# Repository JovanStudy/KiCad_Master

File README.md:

# MOOG_PRODIGY_PROJECT

## 📁 Prototip organizacije

```text
MOOG_PRODIGY_PROJECT/
│
├── schematics/
│   ├── schematics_lvl1/
│   │   └── system_overview.kicad_sch
│   │
│   ├── schematics_lvl2/
│   │   ├── power_supply.kicad_sch
│   │   ├── mcu_core.kicad_sch
│   │   ├── communication.kicad_sch
│   │   └── peripherals.kicad_sch
│   │
│   └── schematics_lvl3/
│       ├── usb_interface.kicad_sch
│       ├── sensors.kicad_sch
│       └── motor_driver.kicad_sch
│
├── pcb/
│   ├── pcb_main.kicad_pcb
│   ├── pcb_panelization.kicad_pcb
│   └── stackup.md
│
├── libraries/
│   ├── symbols/
│   ├── footprints/
│   └── 3d_models/
│
├── bom/   (Bill of Materials – spisak uključenih komponenti)
│   ├── bom.csv
│   └── bom.xlsx
│
├── manufacturing/
│   ├── gerbers/
│   ├── drill/
│   ├── pick_and_place/
│   └── assembly_notes.md
│
├── simulations/
│   ├── spice/
│   └── signal_integrity/
│
└── README.md
```

---

## 📐 PCB Design Rules (EU Baseline)

```text
PCB Design Rules
│
├── Track Width
│   ├── Signal (Single-Width)
│   │   └── 0.20 mm (default, EU safe)
│   │
│   └── Power (Power-Width)
│       ├── 0.50 mm (≤ 1 A)
│       ├── 1.00 mm (2–3 A, 1 oz Cu)
│       └── Polygon Pour (high current)
│
├── Clearance
│   ├── Signal ↔ Signal
│   │   └── 0.20 mm
│   ├── Signal ↔ Power
│   │   └── 0.20 mm
│   ├── Power ↔ Power
│   │   └── 0.20 mm
│   └── High Voltage
│       ├── 230 VAC → ≥ 3.0 mm
│       └── 400 VDC → 4–6 mm (creepage)
│
├── Vias
│   ├── Via Drill
│   │   └── 0.30 mm
│   ├── Via Diameter
│   │   └── 0.60 mm
│   └── Annular Ring
│       └── 0.15 mm
│
├── Pads (THT)
│   ├── Rule
│   │   └── Pad = Drill + 0.6 mm
│   └── Example
│       └── 0.8 mm drill → 1.4 mm pad
│
├── Copper
│   ├── Standard
│   │   └── 1 oz (35 µm)
│   └── Power Boards
│       └── 2 oz (70 µm)
│
└── Solder Mask & Silk
    ├── Mask Expansion
    │   └── 0.05 – 0.10 mm
    ├── Min Silk Width
    │   └── 0.15 mm
    └── Min Text Height
        └── 1.0 mm
```

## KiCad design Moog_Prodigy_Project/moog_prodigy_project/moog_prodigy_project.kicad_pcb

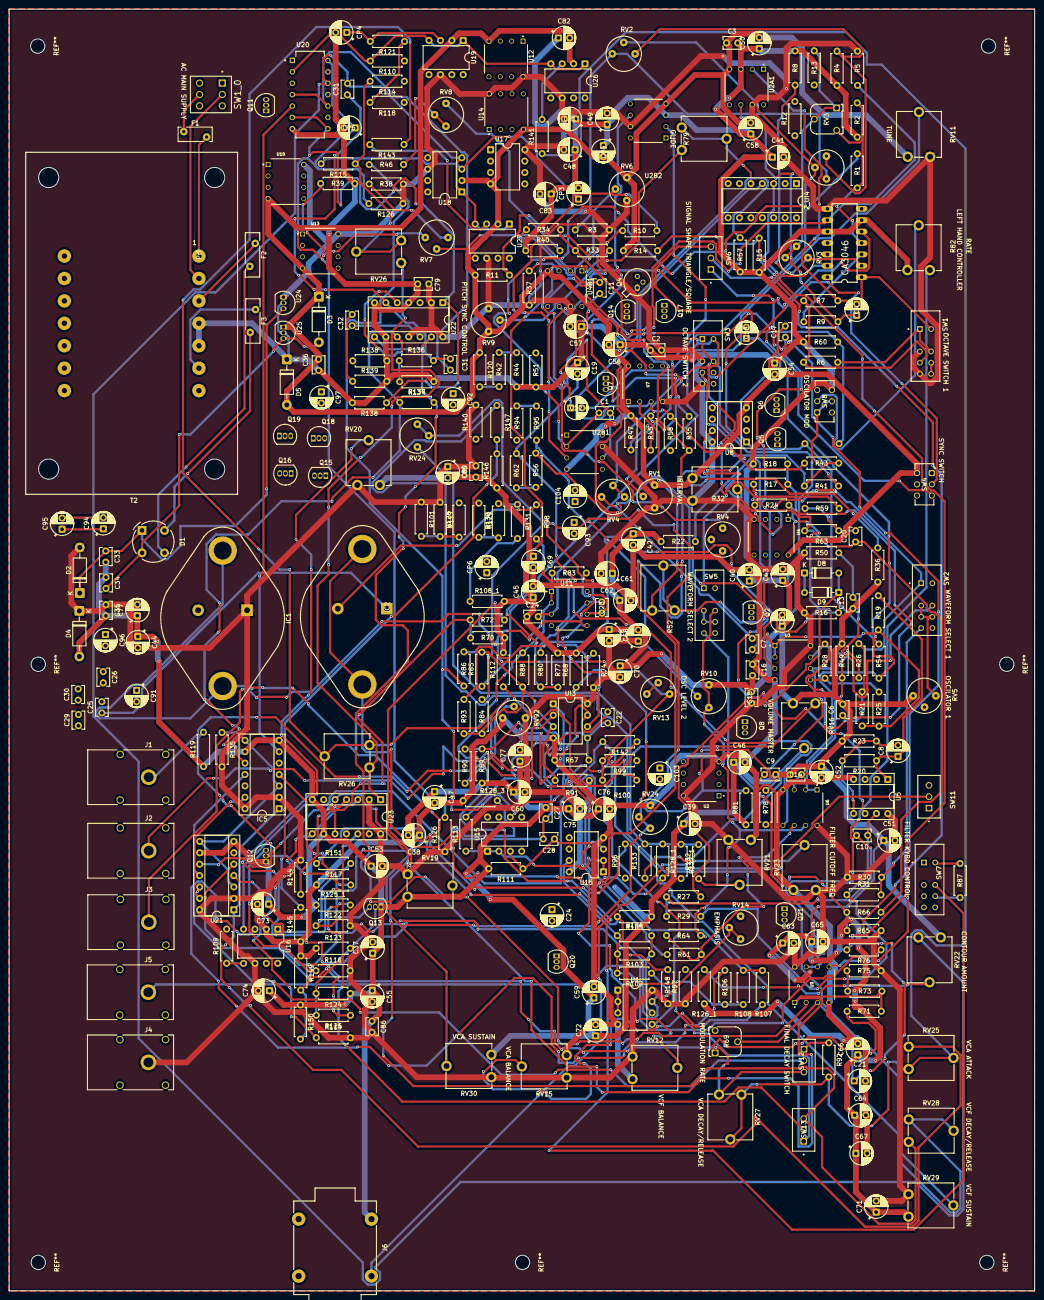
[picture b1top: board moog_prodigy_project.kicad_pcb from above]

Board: 2 copper layers, 228.6 x 285.8 mm, 378 parts (1 on the bottom side), 186 nets.

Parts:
2_UI4: MC14007UBCP; DIP-14_W7.62mm_Socket
C1, C10, C20: 10p; C_Disc_D3.8mm_W2.6mm_P2.50mm
C2, C3, C6, C11, C13, C14, C15, C16, C22, C23, C31, C31#2, C32: 10n; C_Disc_D3.8mm_W2.6mm_P2.50mm
C4, C8, C12, C18: 47p; CP_Radial_D5.0mm_P2.50mm
C5: 1000n; CP_Radial_D5.0mm_P2.50mm
C7, C17: 1n; C_Disc_D3.8mm_W2.6mm_P2.50mm
C9: 500p; C_Disc_D3.8mm_W2.6mm_P2.50mm
C19: 500p; CP_Radial_D5.0mm_P2.50mm
C21: 2u7/25V; CP_Radial_D5.0mm_P2.50mm
C24: 1u/25V; CP_Radial_D5.0mm_P2.50mm
C24#2: 1000n; C_Disc_D3.8mm_W2.6mm_P2.50mm
C25, C26, C27, C29, C30: 27n; C_Disc_D3.8mm_W2.6mm_P2.50mm
C28, C33, C34, C35, C36, C79, C80, C86: 100n; C_Disc_D3.8mm_W2.6mm_P2.50mm
C37, C38, C39, C40, C41, C42, C43, C44, C45, C46, C47, C48, C49, C50, C51, C52, C53, C54, C55, C56, C57, C58, C59, C60, C61, C62, C63, C64, C65, C66, C67, C68, C69, C70, C71, C72, C73, C74, C75, C76, C77, C77#2, C78, C81, C82, C83, C84, C85: 100n; CP_Radial_D5.0mm_P2.50mm
C91, C92: 6u8/25V; CP_Radial_D5.0mm_P2.50mm
C93: 10u/16V; CP_Radial_D5.0mm_P2.50mm
C94, C95: 1000u/35V; CP_Radial_D5.0mm_P2.50mm
C96, C97: 10u/25V; CP_Radial_D5.0mm_P2.50mm
C103: 220u/6V3; CP_Radial_D5.0mm_P2.50mm
C104: 2u2/16V; CP_Radial_D5.0mm_P2.50mm
CA3046: CA3046; DIL14
CP3, CP4: 6.8u; CP_Radial_D5.0mm_P2.50mm
CP5: 10u; CP_Radial_D5.0mm_P2.50mm
CP6: 220u; CP_Radial_D5.0mm_P2.50mm
D1: B40R; Diode_Bridge_Round_D9.0mm
D2, D3, D4, D5: 1N4001; D_DO-41_SOD81_P10.16mm_Horizontal
D8, D9: 1N4148; D_DO-35_SOD27_P7.62mm_Horizontal
F1: 125mA/T; Fuse_Bourns_MF-RHT050
F2, F3: 1A/F; Fuse_Bourns_MF-RHT100
IC1, IC2: 2N3055; TO-3
IC5: MC14007UBCP; DIP-14_W7.62mm_Socket
J1: P2-3; Banana_Cliff_FCR7350B_S16N-PC_Horizontal
J2: P2-4; Banana_Cliff_FCR7350B_S16N-PC_Horizontal
J3: P2-2; Banana_Cliff_FCR7350B_S16N-PC_Horizontal
J4, J5: P2-1; Banana_Cliff_FCR7350B_S16N-PC_Horizontal
J6: NJ2FD-V; Jack_6.35mm_Neutrik_NMJ4HCD2_Horizontal
Q2, Q5, Q6: E112; TO-92_Inline
Q4: BC549; TO-18-3
Q7, Q8, Q11, Q20, Q21: BC549; TO-92_Inline
Q12, Q13: BC327; TO-92_Inline
Q14, Q15, Q16, Q17, Q18, Q19: BC550C; TO-92_Inline
R1: 121K; R_Axial_DIN0207_L6.3mm_D2.5mm_P7.62mm_Horizontal
R2, R8, R36, R40, R83, R106, R108, R111, R112, R115, R121, R126, R126#2, R141, R143: 100; R_Axial_DIN0207_L6.3mm_D2.5mm_P7.62mm_Horizontal
R3: 63K4; R_Axial_DIN0207_L6.3mm_D2.5mm_P7.62mm_Horizontal
R4, R39: 3K01; R_Axial_DIN0207_L6.3mm_D2.5mm_P7.62mm_Horizontal
R5, R9, R27, R37, R38, R59, R73, R75, R86, R88, R97, R116, R122, R132, R133, R139, R144, R148: 100K; R_Axial_DIN0207_L6.3mm_D2.5mm_P7.62mm_Horizontal
R6, R7: 2M; R_Axial_DIN0207_L6.3mm_D2.5mm_P7.62mm_Horizontal
R10, R71: 22K 10%; R_Axial_DIN0207_L6.3mm_D2.5mm_P7.62mm_Horizontal
R11, R47: 15K; R_Axial_DIN0207_L6.3mm_D2.5mm_P7.62mm_Horizontal
R12: 470; R_Axial_DIN0207_L6.3mm_D2.5mm_P7.62mm_Horizontal
R13, R77: 4K75 1%; R_Axial_DIN0207_L6.3mm_D2.5mm_P7.62mm_Horizontal
R14, R16, R50, R110: 20K 5%; R_Axial_DIN0207_L6.3mm_D2.5mm_P7.62mm_Horizontal
R15, R44, R92, R96, R98, R99, R102, R103, R109, R113, R114#2, R118, R142: 1K; R_Axial_DIN0207_L6.3mm_D2.5mm_P7.62mm_Horizontal
R17, R19, R54: 2K; R_Axial_DIN0207_L6.3mm_D2.5mm_P7.62mm_Horizontal
R18: 18K2; R_Axial_DIN0207_L6.3mm_D2.5mm_P7.62mm_Horizontal
R20, R41, R43, R55, R100, R136: 1M; R_Axial_DIN0207_L6.3mm_D2.5mm_P7.62mm_Horizontal
R21, R22, R23, R24, R25, R26, R28, R30, R31, R49, R56, R57, R58, R60, R61, R62, R64, R65, R66, R70, R81, R114, R119, R124, R135, R137, R138, R138#2, R140, R146, R150: 10K; R_Axial_DIN0207_L6.3mm_D2.5mm_P7.62mm_Horizontal
R29: 5M1 1%; R_Axial_DIN0207_L6.3mm_D2.5mm_P7.62mm_Horizontal
R32: 10K LIN; Potentiometer_ACP_CA9-V10_Vertical
R33: 82K5; R_Axial_DIN0207_L6.3mm_D2.5mm_P7.62mm_Horizontal
R34: 120K; R_Axial_DIN0207_L6.3mm_D2.5mm_P7.62mm_Horizontal
R35: 10; R_Axial_DIN0207_L6.3mm_D2.5mm_P7.62mm_Horizontal
R42: 11K8; R_Axial_DIN0207_L6.3mm_D2.5mm_P7.62mm_Horizontal
R45: 22K; R_Axial_DIN0207_L6.3mm_D2.5mm_P7.62mm_Horizontal
R46: 4K75; R_Axial_DIN0207_L6.3mm_D2.5mm_P7.62mm_Horizontal
R51: 1K6 5%; R_Axial_DIN0207_L6.3mm_D2.5mm_P7.62mm_Horizontal
R52, R82: 10K; Potentiometer_ACP_CA9-V10_Vertical
R63, R74, R85: 5M1; R_Axial_DIN0207_L6.3mm_D2.5mm_P7.62mm_Horizontal
R67: 14K3; R_Axial_DIN0207_L6.3mm_D2.5mm_P7.62mm_Horizontal
R68: 18K 5%; R_Axial_DIN0207_L6.3mm_D2.5mm_P7.62mm_Horizontal
R69: 2M5; Potentiometer_Runtron_RM-065_Vertical
R72: 62K 5%; R_Axial_DIN0207_L6.3mm_D2.5mm_P7.62mm_Horizontal
R76: 5M; R_Axial_DIN0207_L6.3mm_D2.5mm_P7.62mm_Horizontal
R78: 30K 5%; R_Axial_DIN0207_L6.3mm_D2.5mm_P7.62mm_Horizontal
R79: 5M1; Potentiometer_ACP_CA9-V10_Vertical
R80: 2K2; R_Axial_DIN0207_L6.3mm_D2.5mm_P7.62mm_Horizontal
R84: 750K; R_Axial_DIN0207_L6.3mm_D2.5mm_P7.62mm_Horizontal
R87, R127_1: 60K4; R_Axial_DIN0207_L6.3mm_D2.5mm_P7.62mm_Horizontal
R89: 43K2; R_Axial_DIN0207_L6.3mm_D2.5mm_P7.62mm_Horizontal
R90: 2M43; R_Axial_DIN0207_L6.3mm_D2.5mm_P7.62mm_Horizontal
R91: 332K; R_Axial_DIN0207_L6.3mm_D2.5mm_P7.62mm_Horizontal
R93: 205K; R_Axial_DIN0207_L6.3mm_D2.5mm_P7.62mm_Horizontal
R94, R95: 120K 5%; R_Axial_DIN0207_L6.3mm_D2.5mm_P7.62mm_Horizontal
R101, R127, R128, R129, R130, R131: 150; R_Axial_DIN0207_L6.3mm_D2.5mm_P7.62mm_Horizontal
R104, R105: 6K81; R_Axial_DIN0207_L6.3mm_D2.5mm_P7.62mm_Horizontal
R107: 51K; R_Axial_DIN0207_L6.3mm_D2.5mm_P7.62mm_Horizontal
R108_1, R120: 200; R_Axial_DIN0207_L6.3mm_D2.5mm_P7.62mm_Horizontal
R117, R123, R145: 56K; R_Axial_DIN0207_L6.3mm_D2.5mm_P7.62mm_Horizontal
R125: 4K3; R_Axial_DIN0207_L6.3mm_D2.5mm_P7.62mm_Horizontal
R125_1: 953; R_Axial_DIN0207_L6.3mm_D2.5mm_P7.62mm_Horizontal
R126_1: 51K 5%; R_Axial_DIN0207_L6.3mm_D2.5mm_P7.62mm_Horizontal
R128_1: 36K; R_Axial_DIN0207_L6.3mm_D2.5mm_P7.62mm_Horizontal
R128_3: 36K 5%; R_Axial_DIN0207_L6.3mm_D2.5mm_P7.62mm_Horizontal
R134: 100k; R_Axial_DIN0207_L6.3mm_D2.5mm_P7.62mm_Horizontal
R147, R151: 4K32; R_Axial_DIN0207_L6.3mm_D2.5mm_P7.62mm_Horizontal
R149: 56K2; R_Axial_DIN0207_L6.3mm_D2.5mm_P7.62mm_Horizontal
RV1, RV4, RV4#2, RV6, RV92: 10K; Potentiometer_Bourns_3339P_Vertical_HandSoldering
RV2, RV2#2, RV3, RV7, RV8: 500; Potentiometer_Bourns_3339P_Vertical_HandSoldering
RV3#2: 500; Potentiometer_Runtron_RM-065_Vertical
RV5, RV9, RV10: 10K LIN; Potentiometer_Bourns_3339P_Vertical_HandSoldering
RV11: 10K LOG; Potentiometer_ACP_CA9-V10_Vertical
RV12, RV15: 100K LIN; Potentiometer_ACP_CA9-V10_Vertical
RV13: 1K; Potentiometer_Bourns_3339P_Vertical_HandSoldering
RV14: 51K1 LOG; Potentiometer_Bourns_3339P_Vertical_HandSoldering
RV16: 5K LOG; Potentiometer_ACP_CA9-V10_Vertical
RV19, RV20: 10K; Potentiometer_ACP_CA9-V10_Vertical
RV21: 100K; Potentiometer_ACP_CA9-V10_Vertical
RV22, RV23: 50K; Potentiometer_ACP_CA9-V10_Vertical
RV24, RV24#2: 250; Potentiometer_Bourns_3339P_Vertical_HandSoldering
RV25, RV26, RV27: 1M LOG; Potentiometer_ACP_CA9-V10_Vertical
RV26#2, RV28: 1M; Potentiometer_ACP_CA9-V10_Vertical
RV29, RV30: 10K LIN; Potentiometer_ACP_CA9-V10_Vertical
SW1, SW2, SW3, SW5, SW7: Switch_4x4; SW_SLW-1575662-5A-S-D
SW1_0: 200MDP1T1B1M2QEH; SW_200MDP1T1B1M2QEH
SW4, SW8: SW_Slide_DPDT_3x3; SW_CK_JS202011CQN_DPDT_Straight
SW6: Switch_1x3; SW_ATE1D-2M3-10-Z
SW11: FILTER MODE; SW_ATE1D-2M3-10-Z
SW12, SW13: FINAL DECAY SWITCH; SW_ATE1D-2M3-10-Z
T2: 230VAC / 2x15VAC 0A53 16VA; Transformer_CHK_EI54-16VA_2xSec
U1, U17: NE5532; DIP-8_W7.62mm
U2, U3, U4, U6, U7, U9, U13: NE5532; DIP794W45P254L1016H508Q8
U2A1, U2B1, U2B2, U4B1, U12, U14: OPA134; DIP794W45P254L959H508Q8
U5, U8: LT1011CN8; DIP-8_W7.62mm_Socket
U10: DIP794W45P254L1016H508Q8
U11: OPA234; DIP794W45P254L959H508Q8
U15, U15#2: LT1469; DIP-8_W7.62mm
U16: LT1228; DIP-8_W7.62mm
U18, U19, U26, U27: OPA184; DIP-8_W7.62mm
U20: NE556N; DIP794W45P254L1930H508Q14
U21, U22, U23: MC14007UBCP; DIP-14_W7.62mm_Socket
U24: LM7812; TO-92_Inline
U25: LM7912; TO-92_Inline
UI3: NE5532; DIP-8_W7.62mm

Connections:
+12V: C2.2, C15.2, C35.1, C37.2, C39.2, C41.2, C43.2, C44.2, C48.2, C49.2, C51.2, C53.2, C55.2, C57.2, C60.2, C62.2, C63.2, C65.2, C68.2, C70.2, C71.2, C74.2, C75.2, C77.2, C77#2.2, C78.1, C79.2, C80.2, C81.2, C83.2, C85.1, C86.2, CA3046.8, D2.2 (A), D4.1 (K), IC1.1 (C), IC5.2, IC5.14, J4.1, R3.1, R5.1, R16.1, R30.2, R32.1, R37.1, R38.1, R50.2, R65.2, R74.2, R75.1, R91.1, R97.1, R101.1, R114.2, R116.2, R122.2, R126.1, R126#2.1, R127.1, R135.2, R140.2, R144.2, R148.2, RV1.1, RV6.1, RV9.1, RV11.1, RV12.3, RV15.3, RV19.3, RV20.3, RV21.1, RV23.1, RV29.3, RV30.3, RV92.3, SW1.2, SW1.4, SW3.2, SW3.4, U1.8, U2.8, U2A1.7, U2B1.7, U2B2.7, U3.8, U4.4, U4B1.7, U5.8, U6.8, U7.4, U8.8, U9.8, U10.8, U12.8, U13.8, U14.8, U15#2.8 (V+), U16.6, U17.8, U18.6 (V+), U19.6 (V+), U21.2, U21.14, U22.2, U22.11, U22.14, U23.2, U23.14, U24.1 (VO), U26.6, U27.6, UI3.8
-12V: C3.1, C16.1, C21.2, C36.2, C38.1, C40.2, C42.2, C45.2, C46.2, C47.2, C50.2, C52.2, C54.2, C56.2, C58.2, C59.2, C61.2, C64.2, C66.2, C67.2, C69.2, C72.2, C73.2, C76.2, C82.2, C84.2, D3.1 (K), D5.2 (A), R11.1, R14.1, R32.3, R47.1, R67.2, R117.1, R120.1, R123.1, R126_1.2, R128_3.1, R145.1, R149.1, RV1.3, RV6.3, RV9.3, RV11.3, RV12.1, RV15.1, RV21.3, RV23.3, RV24.3, RV92.1, SW4.6 (C), U1.4, U2.4, U2A1.4, U2B1.4, U2B2.4, U3.4, U4.8, U4B1.4, U5.4, U6.4, U7.8, U8.4, U9.4, U10.4, U12.4, U13.4, U14.4, U15#2.4 (V-), U16.2, U17.4, U18.2 (V-), U19.2 (V-), U25.1 (VO), U26.2, U27.2, UI3.4
Flag to R87: R46.1, R86.2, UI3.1
Flag to R94: R95.2, RV10.2
Flag to U6A: C8.1, R19.2, R20.1, U5.1
GND: C2.1, C3.2, C5.1, C6.2, C9.1, C13.1, C14.1, C15.1, C16.2, C19.1, C24#2.1, C27.1, C33.2, C34.1, C35.2, C36.1, C37.1, C38.2, C39.1, C40.1, C41.1, C42.1, C43.1, C44.1, C45.1, C46.1, C47.1, C48.1, C49.1, C50.1, C51.1, C52.1, C53.1, C54.1, C55.1, C56.1, C57.1, C58.1, C59.1, C60.1, C61.1, C62.1, C63.1, C64.1, C65.1, C66.1, C67.1, C68.1, C69.1, C70.1, C71.1, C72.1, C73.1, C74.1, C75.1, C76.1, C77.1, C77#2.1, C78.2, C79.1, C80.1, C81.1, C82.1, C83.1, C84.1, C85.2, C86.1, CA3046.6, CA3046.10, CP3.2, CP4.2, CP5.2, D4.2 (A), D5.1 (K), IC5.7, IC5.9, J6.T, Q12.1 (C), Q13.1 (C), R2.2, R4.2, R8.1, R15.1, R18.2, R22.2, R23.2, R36.2, R39.2, R40.1, R44.1, R49.1, R51.2, R57.2, R60.2, R68.2, R70.2, R77.2, R81.1, R82.3, R89.1, R105.1, R108_1.2, R111.2, R112.2, R119.1, R124.1, R125_1.1, R134.1, R138.2, R138#2.2, R139.2, R146.1, R150.1, RV5.3, RV10.3, RV16.1, RV19.1, RV20.1, RV22.3, RV29.1, RV30.1, SW8.4 (A), T2.4 (SB), T2.5 (SC), U2A1.3 (+), U2B2.3 (+), U20.7 (GND), U21.7, U21.9, U22.4, U22.7, U22.9, U23.7, U23.9, U24.2 (GND), U25.2 (GND)
Input to C39: R94.2, R95.1
Input to VCA/VCF: 2_UI4.3, R76.2
Input to diode protection: D8.1 (K), D9.2 (A)
unnamed: 2_UI4.5, R79.2, R79.3
unnamed: R73.1, R75.2
unnamed: C1.2, R10.1, U2B1.6
unnamed: C4.1, R9.1, U2A1.6
unnamed: C7.1, RV4#2.1
unnamed: C10.1, R29.2, R31.1, U5.7
unnamed: C11.2, R45.1, U4B1.6
unnamed: C12.1, U2B2.6
unnamed: C17.1, R52.1, R52.2
unnamed: C18.1, R54.1, R55.1, U8.1
unnamed: C20.1, R63.2, R66.1, U8.7
unnamed: C23.1, R80.2, U11.7
unnamed: C27.2, C28.2, R112.1, U16.1
unnamed: C31.1, C31#2.1, R136.2, U22.6
unnamed: C32.1, U22.12
unnamed: C32.2, R139.1, U22.3
unnamed: RV13.1, RV13.2
unnamed: R98.2, R99.2, R100.1, RV13.3
unnamed: IC2.2 (B), R98.1
unnamed: RV4.2, RV4.3
unnamed: CA3046.2, R8.2, RV3.3
unnamed: CA3046.3, R9.2
unnamed: CA3046.4, R1.2, R2.1, RV3#2.3
unnamed: CA3046.7, R12.2
unnamed: CA3046.13, R14.2, R15.2
unnamed: R40.2, RV8.3
unnamed: R33.2, R34.2, R35.1, R36.1
unnamed: R42.2, R44.2
unnamed: C33.1, D1.1 (+), D2.1 (K), U24.3 (VI)
unnamed: C34.2, D1.2 (-), D3.2 (A), U25.3 (VI)
unnamed: D1.3, F2.2
unnamed: D1.4, F3.2
unnamed: D8.2 (A), D9.1 (K), R84.1
unnamed: F1.1, SW1_0.5
unnamed: IC1.3 (E), R102.2, R103.2, R105.2, R106.2, R108.2
unnamed: R101.2, R127.2, R128.1
unnamed: IC2.3 (E), R96.2
unnamed: C22.2, J1.1, R67.1, UI3.5 (+)
unnamed: C22.1, J2.1, UI3.7
unnamed: J3.1, R74.1, U11.5 (+)
unnamed: J5.1, R76.1
unnamed: J6.S, RV16.2
unnamed: R10.2, R11.2
unnamed: R21.1, R22.1, R24.1, R26.1, R27.1, SW2.1
unnamed: R45.2, R47.2
unnamed: R56.1, R62.1
unnamed: R57.1, R58.1, R59.2, SW5.1, U7.3 (-)
unnamed: Q12.2 (B), R117.2, R119.2
unnamed: Q13.2 (B), R123.2, R124.2, R125.2
unnamed: R128.2, R129.1
unnamed: R129.2, R130.1
unnamed: R130.2, R131.1
unnamed: C25.1, IC2.1 (C)
unnamed: R145.2, R146.2, R147.2
unnamed: R144.1, U23.4
unnamed: R149.2, R150.2, R151.2
unnamed: R148.1, U21.4
unnamed: R1.1, RV1.2
unnamed: R3.2, RV2.1, RV2#2.1
unnamed: R4.1, RV2.3, RV2#2.3
unnamed: R6.1, R7.1, SW1.3
unnamed: R6.2, SW1.1, SW1.6
unnamed: R13.2, RV3.1, RV3.2, RV3#2.1, RV3#2.2
unnamed: R28.2, SW2.6, U3.7
unnamed: R30.1, R31.2, SW2.4
unnamed: R32.2, R33.1
unnamed: R34.1, RV6.2
unnamed: R35.2, SW4.3 (C)
unnamed: R38.2, RV7.1
unnamed: R39.1, RV7.3
unnamed: R41.1, R43.1, SW3.3
unnamed: R41.2, SW3.1, SW3.6
unnamed: R46.2, RV8.1, RV8.2
unnamed: R56.2, R61.1
unnamed: R64.2, RV10.1, SW5.6, U6.7
unnamed: R65.1, R66.2, SW5.4
unnamed: R69.1, R71.2
unnamed: R71.1, R72.1, R73.2, U9.1
unnamed: R77.1, R79.1, R80.1
unnamed: R85.1, RV11.2
unnamed: R87.1, SW7.5
unnamed: R87.2, SW7.7
unnamed: R90.2, RV92.2
unnamed: R100.2, RV12.2
unnamed: R104.1, RV14.1, RV14.2, U1.7, U15#2.7
unnamed: R107.1, RV15.2
unnamed: R109.1, U16.5
unnamed: R113.2, RV16.3
unnamed: R114.1, U23.3, U23.8
unnamed: R42.1, R120.2
unnamed: R125.1, RV20.2
unnamed: R125_1.2, RV24.1, RV24.2, RV24#2.1, RV24#2.2
unnamed: R126_1.1, RV22.2
unnamed: R132.1, RV21.2
unnamed: R133.1, RV23.2
unnamed: IC5.3, IC5.8, R135.1, U21.3, U21.8
unnamed: IC5.10, R137.1, U22.5, U22.10
unnamed: R137.2, U21.10, U22.8, U22.13, U23.10
unnamed: R92.2, R141.1, RV25.1, RV25.2, RV27.2, RV27.3
unnamed: R142.2, R143.1, RV26.1, RV26.2, RV28.2, RV28.3
unnamed: R147.1, RV29.2
unnamed: R151.1, RV30.2
unnamed: RV5.1, SW2.2, SW2.3, SW2.7
unnamed: RV9.2, SW4.2 (B)
unnamed: IC5.1, RV25.3, U21.1
unnamed: RV26.3, RV26#2.3, U23.1
unnamed: SW1.7, SW1.8
unnamed: SW5.2, SW5.3, SW5.7
unnamed: C21.1, R69.2, SW6.1 (A), U9.3 (+)
unnamed: SW6.2 (B), U9.5 (+)
unnamed: R78.1, R81.2, SW6.3 (C)
unnamed: R128_1.2, R128_3.2, SW11.2 (B)
unnamed: R92.1, SW12.1 (A)
unnamed: SW12.2 (B), U21.12
unnamed: RV27.1, SW12.3 (C), U21.5
unnamed: R142.1, SW13.1 (A)
unnamed: SW13.2 (B), U23.12
unnamed: RV28.1, SW13.3 (C), U23.5
unnamed: F1.2, T2.1 (AA)
unnamed: SW1_0.2, T2.2 (AB)
unnamed: F2.1, T2.3 (SA)
unnamed: F3.1, T2.6 (SD)
unnamed: R102.1, U1.5 (+)
unnamed: R103.1, R104.2, U1.6 (-)
unnamed: C4.2, CA3046.1, R7.2, SW1.5, U2A1.2 (-)
unnamed: CA3046.9, R5.2, U2B1.3 (+)
unnamed: C1.1, RV2.2, RV2#2.2, U2B1.2 (-)
unnamed: C12.2, R43.2, SW3.5, U2B2.2 (-)
unnamed: C5.2, R16.2, R17.1, U3.3 (+)
unnamed: C7.2, R19.1, R21.2, R25.1, U3.1, U3.2 (-)
unnamed: R25.2, R28.1, U3.5 (+)
unnamed: C9.2, R26.2, U3.6 (-)
unnamed: CA3046.5, RV4#2.2, RV4#2.3
unnamed: R37.2, U4B1.3 (+)
unnamed: C11.1, RV7.2, U4B1.2 (-)
unnamed: C8.2, R20.2, R23.1, U5.5 (+)
unnamed: R24.2, U5.6 (-)
unnamed: C10.2, R27.2, R29.1
unnamed: C6.1, R17.2, R18.1
unnamed: C13.2, C14.2, R49.2, R50.1, U6.3 (+)
unnamed: C17.2, R54.2, U6.1, U6.2 (-)
unnamed: C19.2, R62.2, U6.5 (+)
unnamed: R61.2, R64.1, U6.6 (-)
unnamed: R52.3, U7.2 (+)
unnamed: C18.2, R55.2, R60.1
unnamed: C20.2, R59.1, R63.1
unnamed: R70.1, R72.2, U9.2 (-)
unnamed: R82.1, U9.6 (-), U9.7
unnamed: 2_UI4.4, C24#2.2, U11.3 (+)
unnamed: R83.1, R88.1, SW7.6, U11.1, U11.2 (-)
unnamed: C23.2, R83.2, U11.6 (-)
unnamed: C28.1, R111.1, U15.3 (+), U15#2.3 (+)
unnamed: R113.1, U15.1, U15.2 (-), U15#2.1, U15#2.2 (-)
unnamed: R106.1, U16.3 (+)
unnamed: R107.2, R108.1, U16.4 (-)
unnamed: CP3.1, R115.2, U18.3 (+)
unnamed: CP4.1, R121.2, U19.3 (+)
unnamed: CP5.1, R126.2, R126#2.2, U20.14 (VCC)
unnamed: R141.2, U26.3 (+)
unnamed: R143.2, U27.3 (+)
unnamed: R84.2, R85.2, R86.1, R88.2, R91.2, R93.2, UI3.3 (+)
unnamed: R89.2, R90.1, UI3.2 (-)
unnamed: R68.1, UI3.6 (-)
ON: R93.1, SW8.1 (A), SW8.5 (B)
OSC MOD SWITCH: R82.2, SW8.2 (B)
OUTPUT_1: IC5.6, U20.5 (1OUT)
RESET: C31#2.2, U20.4 (1RESET), U20.10 (2RESET)
THRESHOLD_1: R110.2, U19.1, U19.4 (-), U20.2 (1THRES), U26.1, U26.4 (-)
THRESHOLD_2: C31.2, RV22.1, U18.1, U18.4 (-), U20.12 (2THRES), U27.1, U27.4 (-)
TRIGGER: R138#2.1, U20.6 (1TRIG), U20.8 (2TRIG), U22.1
node_1: R108_1.1, R131.2
node_2: R127_1.1, R128_1.1, R132.2, R133.2, RV24#2.3
node_8: R118.2, R121.1
node_10: IC5.4, Q13.3 (E), R122.1
node_11: R114#2.2, R115.1, RV26#2.1, RV26#2.2
node_13: Q12.3 (E), R116.1
to_VCA/VCF: R134.2, R136.1

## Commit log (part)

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2026-02-06 Prvi commit
2026-02-06 README.md message update
2026-02-06 README.md update 2
2026-02-06 README.md update 3
2026-03-15 KiCad organizovanje foldera i fajlova u segmente
2026-03-20 First part of left schematic update + symbol creation
2026-03-20 Middle part of left side update 20.03.2026
2026-03-26 Final part of left side 26.03.2026
2026-03-29 Final part of left side pt.2 29.03.2026
2026-04-06 +12V & -12V fix flags
2026-04-07 Imoprt LF393 & Sortiranje fleg-ova 07.04.2026
2026-04-09 Potrebno je da se uradi jos zamena za 4007, dal ubaciti pojedinacne mosfete ili ima vec neko integrisano kolo koje je slicno tome, koje parametre gledati
2026-04-09 LT1227 added
2026-04-09 LF353 & UI3046 zamena
2026-04-11 Dodavanje evropskih komponenti u semu 11.04.2026
2026-04-12 LM393BIPWR izmena, dodavanje spoljnih delova pt.2, 12.04.2026
2026-04-18 Dodato zamena za 4007, bolje karakteristike po pitanju brzine samih fetova, nebaferovani (UB) zato sto nam treba linearna komponenta
2026-04-21 Zamena komponenti
2026-04-22 Update dokumentacije
2026-04-22 KiCad smybols import CA3046
2026-04-24 Vcc fix, banana jack, connector, OP adding top sch
2026-04-25 4007 update, impor biblioteka LM 393
2026-04-27 Zamena fet-ova E112 sa BF256C + update dokumentacije
2026-04-27 New update footprints
2026-04-27 BC327 i LT1469
2026-04-27 Footprints fix test
2026-04-27 Footpring fix 2
2026-04-28 Footprint update new 28.04.2026
2026-04-29 Footprints import new 29.04.2026
2026-04-30 transformator i prekidac
2026-04-30 pokusaj merga
2026-04-30 staaaa
2026-05-01 Spajanje projekta final 1
2026-05-01 PCB priprema i fix gresaka
2026-05-02 problemi sa ca3096, multiplicirani footprintovi
2026-05-05 obrisani log fajlovi
2026-05-05 CA3046 leva strana seme update
2026-05-08 Left side PCB update final
2026-05-11 SMD component to THT component update PCB
2026-05-11 raspored i edge cut
2026-05-17 Routhed PCB final 17.05.2026
2026-05-21 Mounting holes implementation
2026-05-27 Fix 1 nakon review-a 27.05.2026
2026-06-05 Latest checkpoints update 05.06.2026
2026-06-26 27.06.2026 - dodavanje izmena sa konsultacija
